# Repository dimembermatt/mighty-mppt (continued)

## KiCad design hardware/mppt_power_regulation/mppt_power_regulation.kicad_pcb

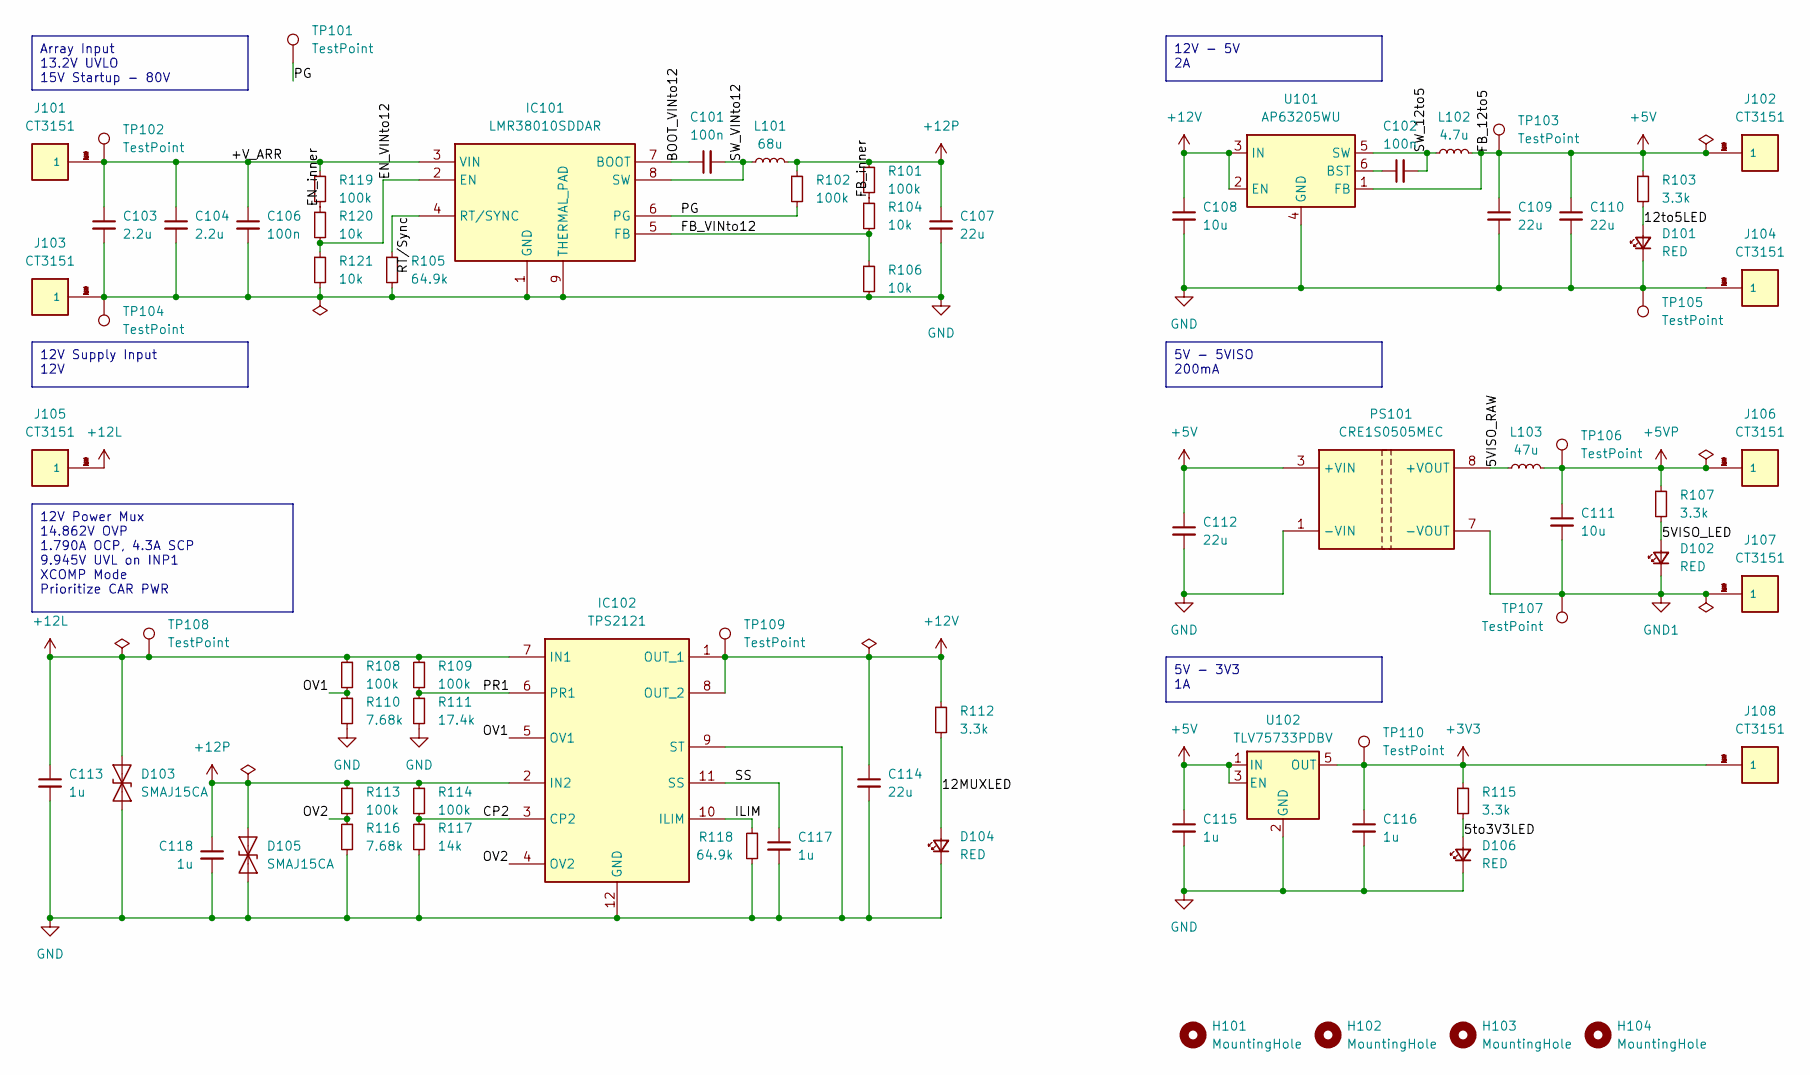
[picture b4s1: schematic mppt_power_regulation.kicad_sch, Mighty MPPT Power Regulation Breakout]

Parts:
C101, C102, C106: 100n; C_0805_2012Metric_Pad1.18x1.45mm_HandSolder
C103, C104: 2.2u; R_1206_3216Metric_Pad1.30x1.75mm_HandSolder
C107, C109, C110, C112, C114: 22u; C_0805_2012Metric_Pad1.18x1.45mm_HandSolder
C108, C111: 10u; C_0805_2012Metric_Pad1.18x1.45mm_HandSolder
C113, C115, C116, C117, C118: 1u; C_0805_2012Metric_Pad1.18x1.45mm_HandSolder
D101, D102, D104, D106: RED; LED_0805_2012Metric_Pad1.15x1.40mm_HandSolder
D103, D105: SMAJ15CA; D_SMA
H101, H102, H103, H104: MountingHole; MountingHole_5.3mm_M5
IC101: LMR38010SDDAR; ti_LMR38010_SDDAR
IC102: TPS2121; ti_TPS2121_RUXR
J101, J102, J103, J104, J105, J106, J107, J108: CT3151; caltest_ct3151
L101: 68u; L_Bourns_SRN6045TA
L102: 4.7u; L_Bourns_SRN6045TA
L103: 47u; L_Bourns_SRN6045TA
PS101: CRE1S0505MEC; murata_CRE1_S0505MEC
R101, R102, R108, R109, R113, R114, R119: 100k; R_0805_2012Metric_Pad1.20x1.40mm_HandSolder
R103, R107, R112, R115: 3.3k; R_0805_2012Metric_Pad1.20x1.40mm_HandSolder
R104, R106, R120, R121: 10k; R_0805_2012Metric_Pad1.20x1.40mm_HandSolder
R105, R118: 64.9k; R_0805_2012Metric_Pad1.20x1.40mm_HandSolder
R110, R116: 7.68k; R_0805_2012Metric_Pad1.20x1.40mm_HandSolder
R111: 17.4k; R_0805_2012Metric_Pad1.20x1.40mm_HandSolder
R117: 14k; R_0805_2012Metric_Pad1.20x1.40mm_HandSolder
TP101, TP102, TP103, TP104, TP105, TP106, TP107, TP108, TP109, TP110: TestPoint; TestPoint_Keystone_5000-5004_Miniature
U101: AP63205WU; TSOT-23-6_HandSoldering
U102: TLV75733PDBV; SOT-23-5_HandSoldering

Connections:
+3V3: C116.1, J108.1, J108.2 (1), J108.3 (1), J108.4 (1), R115.1, TP110.1, U102.5 (OUT)
+5V: C109.1, C110.1, C112.1, C115.1, J102.1, J102.2 (1), J102.3 (1), J102.4 (1), L102.2, PS101.3 (+VIN), R103.1, TP103.1, U101.1 (FB), U102.1 (IN), U102.3 (EN)
+5VP: C111.1, J106.1, J106.2 (1), J106.3 (1), J106.4 (1), L103.2, R107.1, TP106.1
+12L: C113.1, D103.2 (A2), IC102.7 (IN1), J105.1, J105.2 (1), J105.3 (1), J105.4 (1), R108.1, R109.1, TP108.1
+12P: C107.1, C118.1, D105.2 (A2), IC102.2 (IN2), L101.2, R101.1, R102.1, R113.1, R114.1
+12V: C108.1, C114.1, IC102.1 (OUT_1), IC102.8 (OUT_2), R112.1, TP109.1, U101.2 (EN), U101.3 (IN)
/5VISO_LED: D102.2 (A), R107.2
/5VISO_RAW: L103.1, PS101.8 (+VOUT)
/5to3V3LED: D106.2 (A), R115.2
/12MUXLED: D104.2 (A), R112.2
/12to5LED: D101.2 (A), R103.2
/+V_ARR: C103.1, C104.1, C106.1, IC101.3 (VIN), J101.1, J101.2 (1), J101.3 (1), J101.4 (1), R119.1, TP102.1
/BOOT_VINto12: C101.1, IC101.7 (BOOT)
/CP2: IC102.3 (CP2), R114.2, R117.1
/EN_VINto12: IC101.2 (EN), R120.2, R121.1
/EN_inner: R119.2, R120.1
/FB_VINto12: IC101.5 (FB), R104.2, R106.1
/FB_inner: R101.2, R104.1
/ILIM: IC102.10 (ILIM), R118.1
/OV1: IC102.5 (OV1), R108.2, R110.1
/OV2: IC102.4 (OV2), R113.2, R116.1
/PG: IC101.6 (PG), R102.2, TP101.1
/PR1: IC102.6 (PR1), R109.2, R111.1
/RT/Sync: IC101.4 (RT/SYNC), R105.1
/SS: C117.1, IC102.11 (SS)
/SW_12to5: C102.2, L102.1, U101.5 (SW)
/SW_VINto12: C101.2, IC101.8 (SW), L101.1
GND: C103.2, C104.2, C106.2, C107.2, C108.2, C109.2, C110.2, C112.2, C113.2, C114.2, C115.2, C116.2, C117.2, C118.2, D101.1 (K), D103.1 (A1), D104.1 (K), D105.1 (A1), D106.1 (K), IC101.1 (GND), IC101.9 (THERMAL_PAD), IC102.9 (ST), IC102.12 (GND), J103.1, J103.2 (1), J103.3 (1), J103.4 (1), J104.1, J104.2 (1), J104.3 (1), J104.4 (1), PS101.1 (-VIN), R105.2, R106.2, R110.2, R111.2, R116.2, R117.2, R118.2, R121.2, TP104.1, TP105.1, U101.4 (GND), U102.2 (GND)
GND1: C111.2, D102.1 (K), J107.1, J107.2 (1), J107.3 (1), J107.4 (1), PS101.7 (-VOUT), TP107.1
unnamed: C102.1, U101.6 (BST)

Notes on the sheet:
5V - 3V3 1A
5V - 5VISO 200mA
Array Input 13.2V UVLO 15V Startup - 80V
12V Power Mux 14.862V OVP 1.790A OCP, 4.3A SCP 9.945V UVL on INP1 XCOMP Mode Prioritize CAR PWR
12V - 5V 2A
12V Supply Input 12V

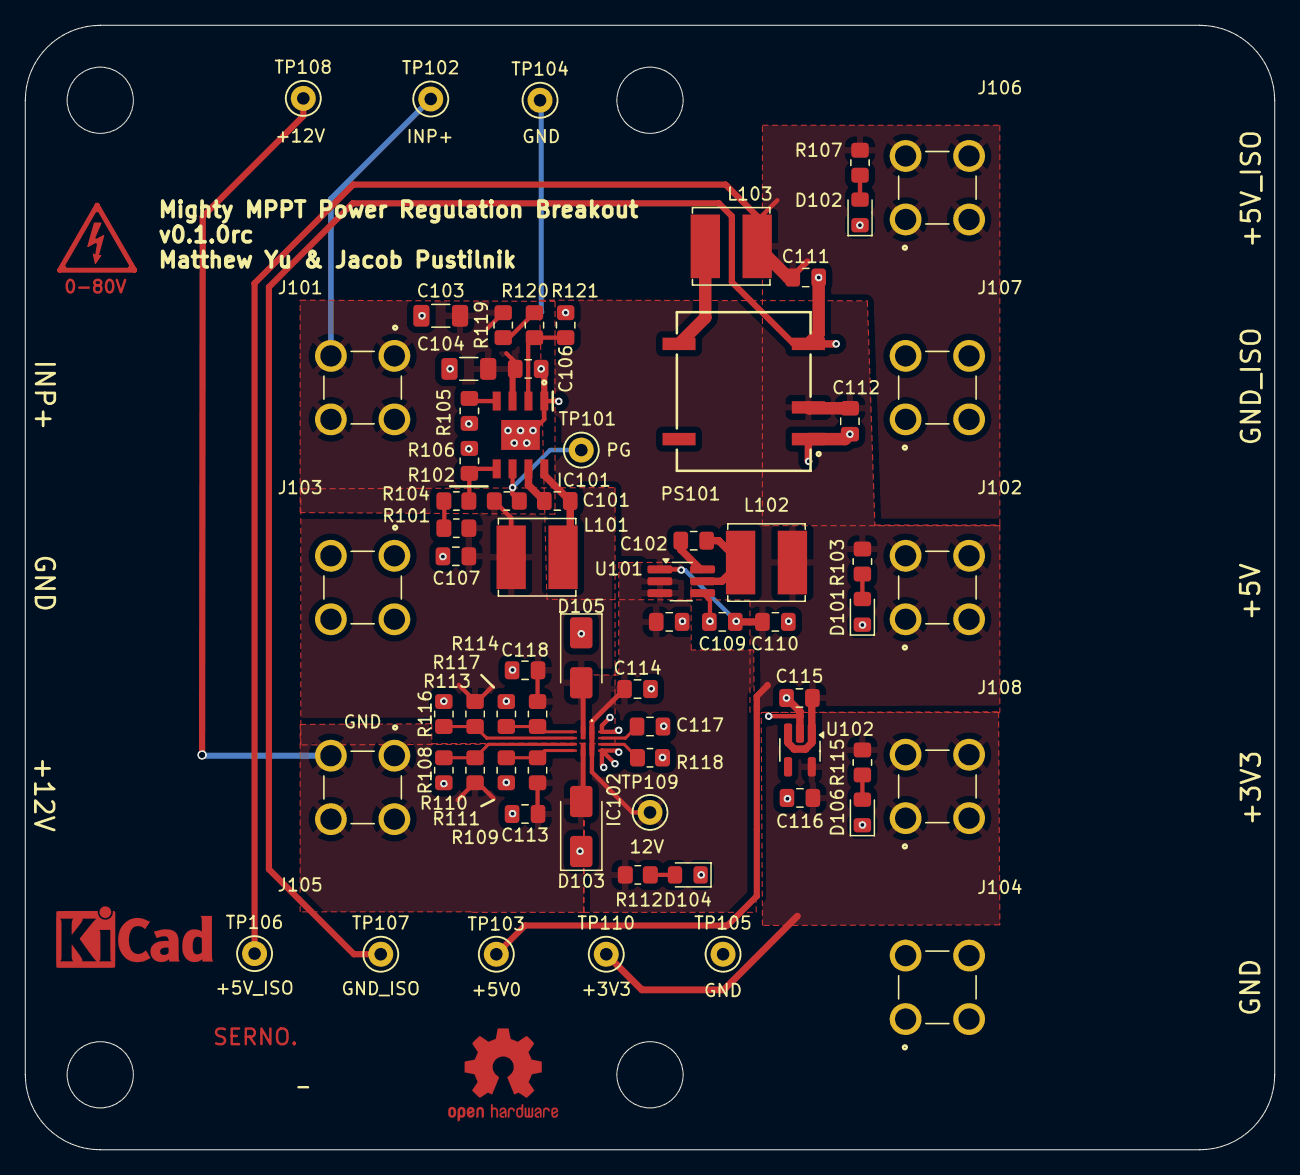
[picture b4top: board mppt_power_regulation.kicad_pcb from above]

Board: 2 copper layers, 100.0 x 90.0 mm, 74 parts (0 on the bottom side), 30 nets.

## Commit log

2024-08-25 Rename LICENSE to SOFTWARE_LICENSE
2024-08-25 Rename HARDWARE_LICENSE.txt to HARDWARE_LICENSE
2024-08-25 power regulation breakout v0.1.0 rc
2024-08-25 remove redundant output folder
2024-08-25 gave names to unlabeled nets
2024-08-25 moved testpoints from between connectors to free space on board, added labels under banana jacks
2024-08-25 Converter breakout.
2024-08-26 update bom to remove lcsc dependency
2024-08-26 changed layout of switching loop planes, added small 100n capacitors on HV input and output
2024-08-26 changed shapes of converter power planes, added small 100n capacitors to HV input and output capacitance
2024-08-27 init schematic for controller and power path
2024-08-27 system block diagram
2024-08-27 fix drc errors introduced into converter, power reg
2024-08-28 revise sch and bom for power path, prelim layout, prelim documentation structure
2024-08-28 init sch build of main project
2024-09-01 run through mppt sch, going through bom
2024-09-01 update final missing pieces for sch, moving to bom pop
2024-09-02 bom consolidated, starting layout
2024-09-02 progress on layout
2024-09-03 placement of majority of power path
2024-09-07 PCB variant for power regulation breakout.
2024-09-08 complete layout, drc, signaling optimizations and added dnp testpoints
2024-09-21 converter schematic and layout.
2024-09-21 unset dnp for all components in sch
2024-09-21 pull in tft, power reg layouts
2024-09-22 remove testpoints, integrat 60% of layout
2024-09-28 swap can net tie to solder bridge for iso, 80% done layout
